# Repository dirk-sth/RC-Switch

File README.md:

# RC-Switch
RC-Switch als 1 Kanal und 2 Kanal Version

1 Kanal Version - In Bearbeitung

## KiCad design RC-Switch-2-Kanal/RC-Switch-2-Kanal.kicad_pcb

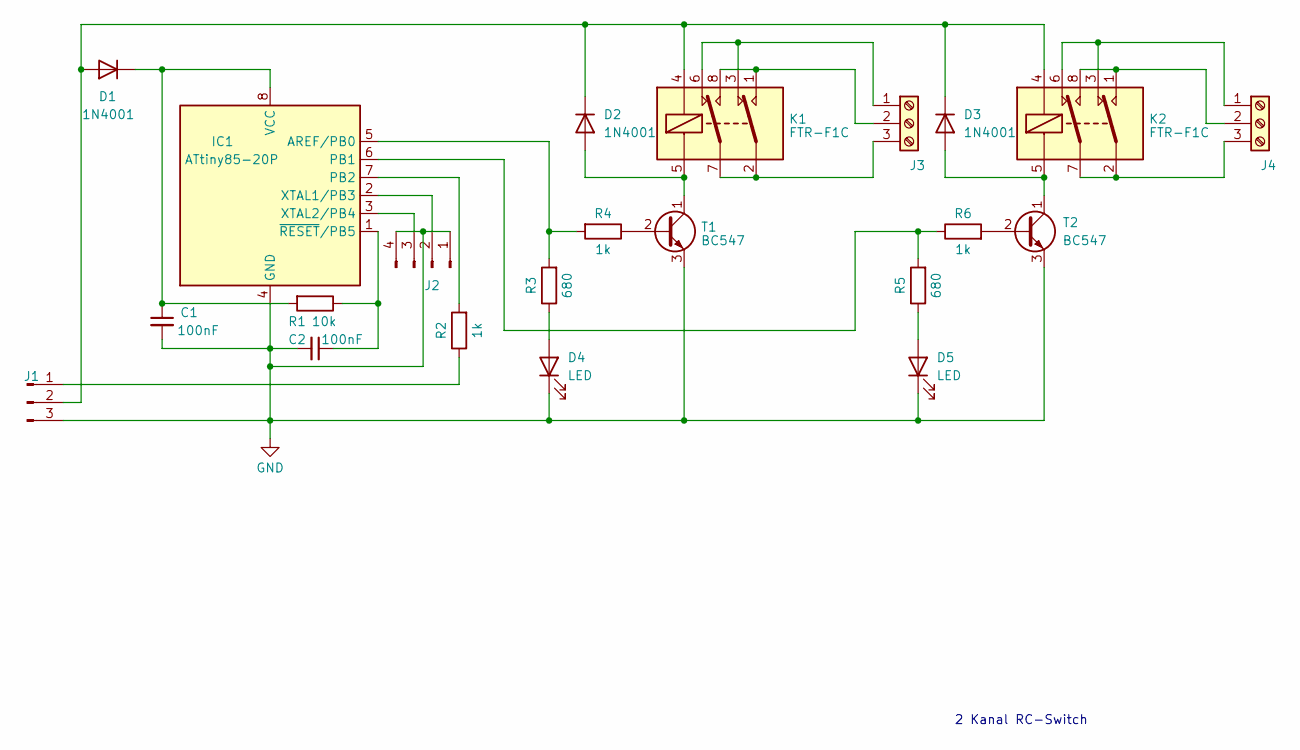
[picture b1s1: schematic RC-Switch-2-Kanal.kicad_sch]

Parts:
C1, C2: 100nF; C_Rect_L7.0mm_W2.0mm_P5.00mm
D1, D2, D3: 1N4001; D_DO-41_SOD81_P10.16mm_Horizontal
D4, D5: LED; LED_D3.0mm
IC1: ATtiny85-20P; DIP-8_W7.62mm
J1: Conn_01x03_Pin; PinSocket_1x03_P2.54mm_Vertical
J2: PinHeader_1x04_P2.54mm_Vertical
J3, J4: Screw_Terminal_01x03; TerminalBlock_bornier-3_P5.08mm
K1, K2: FTR-F1C; Relay_DPDT_Fujitsu_FTR-F1C
R1: 10k; R_Axial_DIN0207_L6.3mm_D2.5mm_P10.16mm_Horizontal
R2, R4, R6: 1k; R_Axial_DIN0207_L6.3mm_D2.5mm_P10.16mm_Horizontal
R3, R5: 680; R_Axial_DIN0207_L6.3mm_D2.5mm_P10.16mm_Horizontal
T1, T2: BC547; TO-92L_HandSolder

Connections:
GND: C1.2, C2.2, D4.1 (K), D5.1 (K), IC1.4 (GND), J1.3, J2.1, J2.4, T1.3 (E), T2.3 (E)
unnamed: D1.2 (A), D2.1 (K), D3.1 (K), J1.2, K1.4, K2.4
unnamed: C1.1, D1.1 (K), IC1.8 (VCC), R1.2
unnamed: D2.2 (A), K1.5, T1.1 (C)
unnamed: D3.2 (A), K2.5, T2.1 (C)
unnamed: D4.2 (A), R3.1
unnamed: D5.2 (A), R5.1
unnamed: IC1.5 (AREF/PB0), R3.2, R4.2
unnamed: IC1.6 (PB1), R5.2, R6.1
unnamed: IC1.7 (PB2), R2.2
unnamed: IC1.2 (XTAL1/PB3), J2.2
unnamed: IC1.3 (XTAL2/PB4), J2.3
unnamed: C2.1, IC1.1 (~RESET/PB5), R1.1
unnamed: J1.1, R2.1
unnamed: J3.1, K1.3, K1.6
unnamed: J3.2, K1.1, K1.8
unnamed: J3.3, K1.2, K1.7
unnamed: J4.1, K2.3, K2.6
unnamed: J4.2, K2.1, K2.8
unnamed: J4.3, K2.2, K2.7
unnamed: R4.1, T1.2 (B)
unnamed: R6.2, T2.2 (B)

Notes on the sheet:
2 Kanal RC-Switch

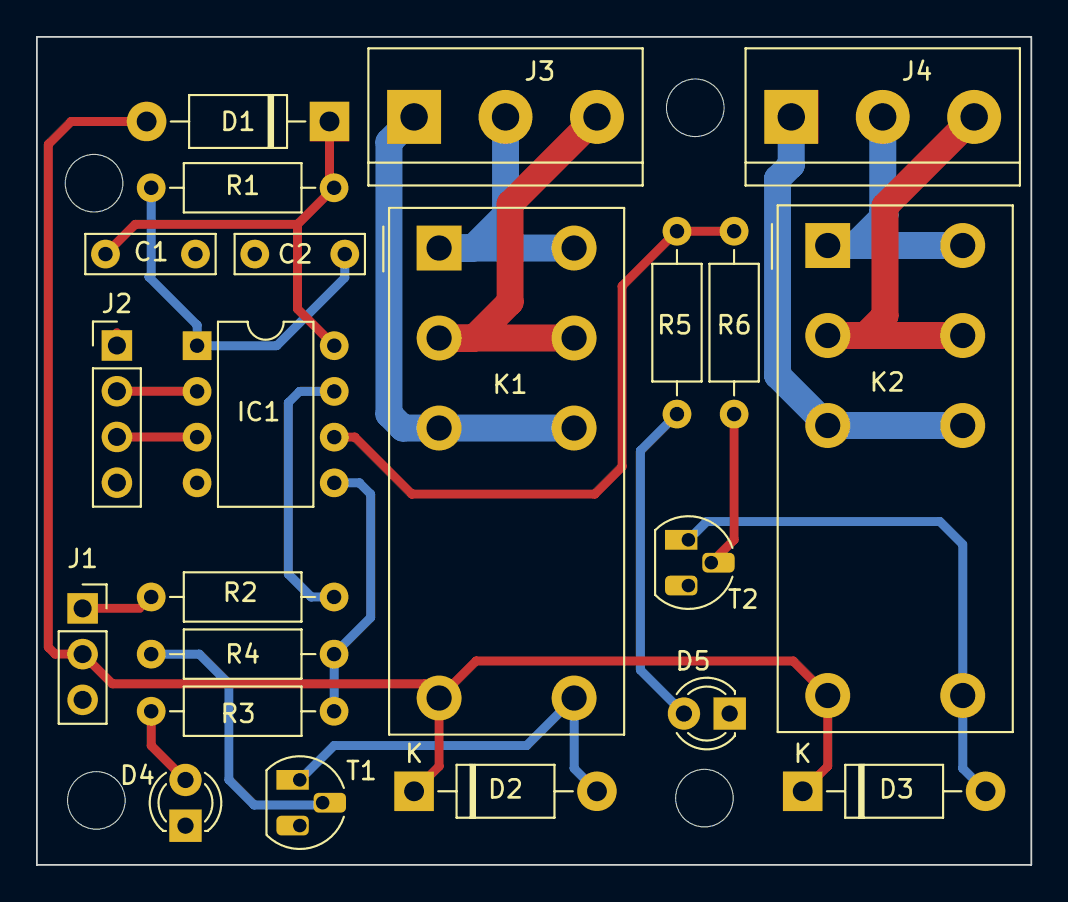
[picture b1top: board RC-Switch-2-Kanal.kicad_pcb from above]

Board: 2 copper layers, 55.2 x 46.0 mm, 22 parts (0 on the bottom side), 22 nets.

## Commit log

2024-02-03 test
2024-02-03 Anpassung
2024-02-05 test neuer notebook
2024-02-05 test2
2024-02-09 Rename ReadMe.md to README.md
2024-02-10 Umbau des Repository
2024-02-10 Erweiterung 1 Kanalversion
2024-02-16 Anpassung Readme.md
